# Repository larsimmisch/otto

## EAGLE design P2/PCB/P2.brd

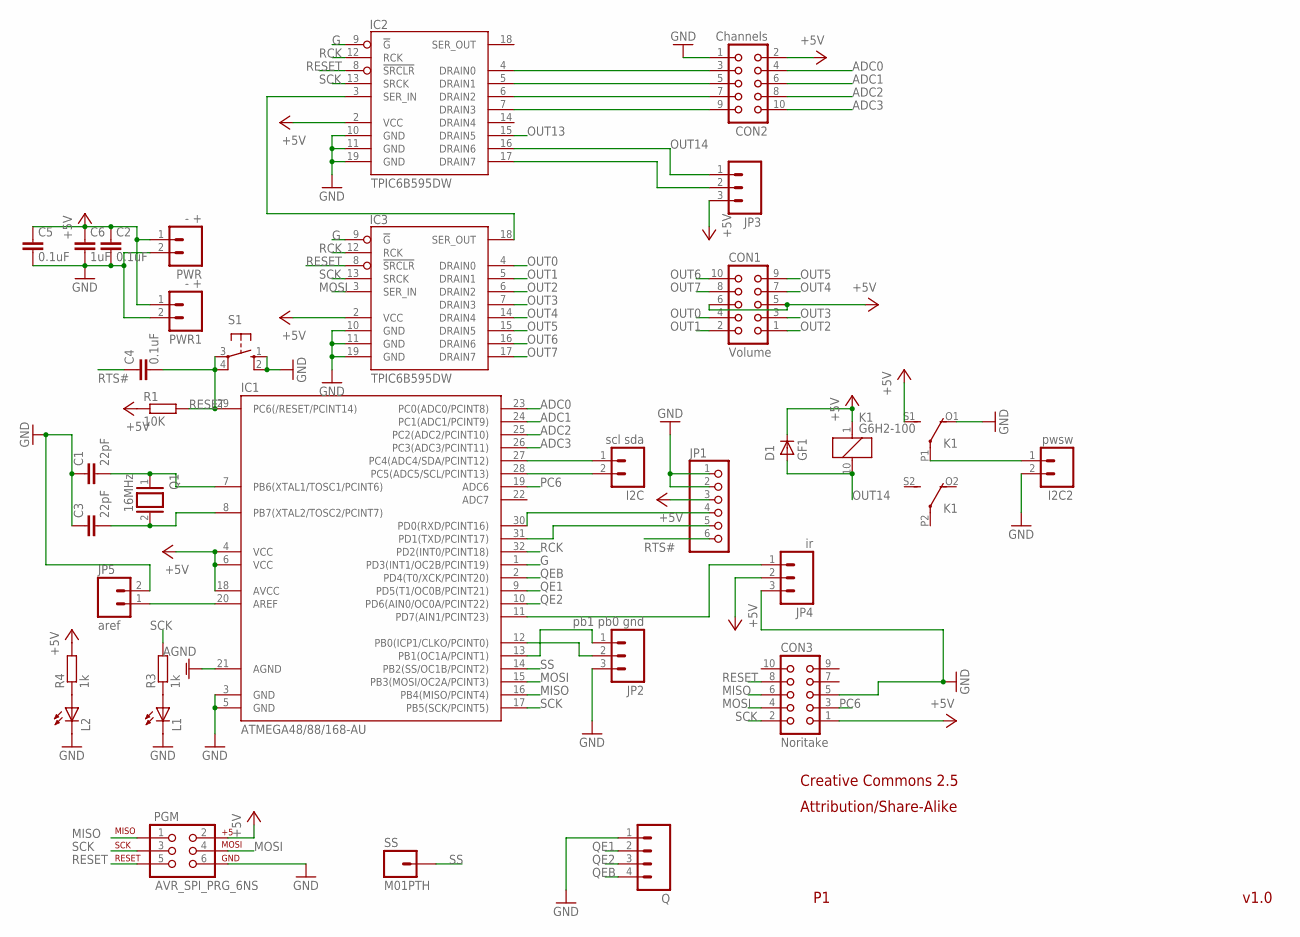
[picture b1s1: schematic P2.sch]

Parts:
C1, C3: 22pF; C0805
C2, C4, C5: 0.1uF; C0805
C6: 1uF; C0805
CON1: Volume; CON10L
CON2: Channels; CON10L
CON3: Noritake; CON10L
D1: GF1; SMA-DO214AC
I2C: scl sda; 1X02
I2C2: pwsw; 1X02
IC1: ATMEGA48/88/168-AU; TQFP32-08
IC2, IC3: TPIC6B595DW; SO20W
JP1: PINHD-1X6CLEAN; 1X06-CLEAN
JP2: pb1 pb0 gnd; 1X03
JP3: M03PTH; 1X03
JP4: ir; 1X03
JP5: aref; 1X02
K1: G6H2-100
L1, L2: LEDSML0805; SML0805
PGM: AVR_SPI_PRG_6NS; 2X3-NS
PWR, PWR1: - +; 1X02
Q: M04PTH; 1X04
Q1: 16MHz; QS
R1: 10K; M0805
R3, R4: 1k; M0805
S1: 10-XX; B3F-10XX
SS: M01PTH; 1X01

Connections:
+5V: C2.1, C5.1, C6.1, CON1.5, CON1.6, CON2.2, CON3.1, D1.K (C), IC1.4 (VCC), IC1.6 (VCC), IC1.18 (AVCC), IC2.2 (VCC), IC3.2 (VCC), JP1.3, JP3.3, JP4.2, K1.1, K1.S1 (S), PGM.2, PWR.1, PWR1.1, R1.1, R4.2
ADC0: CON2.4, IC1.23 (PC0(ADC0/PCINT8))
ADC1: CON2.6, IC1.24 (PC1(ADC1/PCINT9))
ADC2: CON2.8, IC1.25 (PC2(ADC2/PCINT10))
ADC3: CON2.10, IC1.26 (PC3(ADC3/PCINT11))
AGND: IC1.21 (AGND)
G: IC1.1 (PD3(INT1/OC2B/PCINT19)), IC2.9 (!G), IC3.9 (!G)
GND: C1.1, C2.2, C3.1, C5.2, C6.2, CON2.1, CON3.5, I2C2.2, IC1.3 (GND), IC1.5 (GND), IC2.10 (GND), IC2.11 (GND), IC2.19 (GND), IC3.10 (GND), IC3.11 (GND), IC3.19 (GND), JP1.1, JP1.2, JP2.3, JP4.3, JP5.2, K1.O1 (O), L1.C, L2.C, PGM.6, PWR.2, PWR1.2, Q.1, S1.1 (S), S1.2 (S1)
MISO: CON3.6, IC1.16 (PB4(MISO/PCINT4)), PGM.1
MOSI: CON3.4, IC1.15 (PB3(MOSI/OC2A/PCINT3)), IC3.3 (SER_IN), PGM.4
unnamed: C1.2, IC1.7 (PB6(XTAL1/TOSC1/PCINT6)), Q1.1
unnamed: C3.2, IC1.8 (PB7(XTAL2/TOSC2/PCINT7)), Q1.2
unnamed: IC1.30 (PD0(RXD/PCINT16)), JP1.4
unnamed: IC1.31 (PD1(TXD/PCINT17)), JP1.5
unnamed: I2C2.1, K1.P1
unnamed: IC2.3 (SER_IN), IC3.18 (SER_OUT)
unnamed: I2C.1, IC1.27 (PC4(ADC4/SDA/PCINT12))
unnamed: I2C.2, IC1.28 (PC5(ADC5/SCL/PCINT13))
unnamed: IC1.13 (PB1(OC1A/PCINT1)), JP2.1
unnamed: IC1.12 (PB0(ICP1/CLKO/PCINT0)), JP2.2
unnamed: IC2.17 (DRAIN7), JP3.2
unnamed: IC1.20 (AREF), JP5.1
unnamed: IC1.11 (PD7(AIN1/PCINT23)), JP4.1
unnamed: L1.A, R3.1
unnamed: L2.A, R4.1
OUT0: CON1.4, IC3.4 (DRAIN0)
OUT1: CON1.2, IC3.5 (DRAIN1)
OUT2: CON1.1, IC3.6 (DRAIN2)
OUT3: CON1.3, IC3.7 (DRAIN3)
OUT4: CON1.7, IC3.14 (DRAIN4)
OUT5: CON1.9, IC3.15 (DRAIN5)
OUT6: CON1.10, IC3.16 (DRAIN6)
OUT7: CON1.8, IC3.17 (DRAIN7)
OUT8: CON2.3, IC2.4 (DRAIN0)
OUT9: CON2.5, IC2.5 (DRAIN1)
OUT10: CON2.7, IC2.6 (DRAIN2)
OUT11: CON2.9, IC2.7 (DRAIN3)
OUT13: IC2.15 (DRAIN5)
OUT14: D1.A, IC2.16 (DRAIN6), JP3.1, K1.10 (2)
PC6: CON3.3, IC1.19 (ADC6)
QE1: IC1.9 (PD5(T1/OC0B/PCINT21)), Q.2
QE2: IC1.10 (PD6(AIN0/OC0A/PCINT22)), Q.3
QEB: IC1.2 (PD4(T0/XCK/PCINT20)), Q.4
RCK: IC1.32 (PD2(INT0/PCINT18)), IC2.12 (RCK), IC3.12 (RCK)
RESET: C4.2, CON3.8, IC1.29 (PC6(/RESET/PCINT14)), IC2.8 (!SRCLR), IC3.8 (!SRCLR), PGM.5, R1.2, S1.3, S1.4 (P1)
RTS#: C4.1, JP1.6
SCK: CON3.2, IC1.17 (PB5(SCK/PCINT5)), IC2.13 (SRCK), IC3.13 (SRCK), PGM.3, R3.2
SS: IC1.14 (PB2(SS/OC1B/PCINT2)), SS.1

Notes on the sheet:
v1.0
Creative Commons 2.5
Attribution/Share-Alike

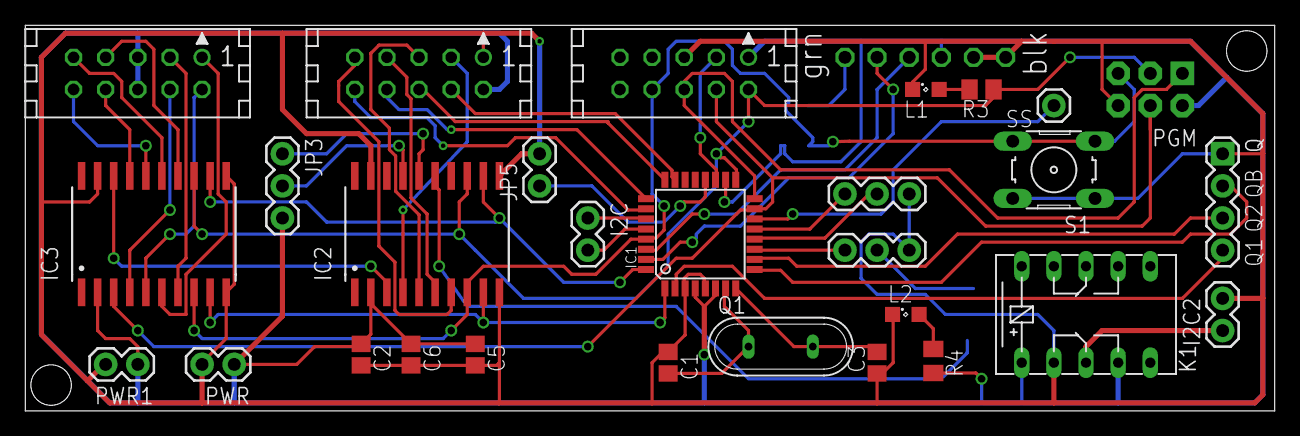
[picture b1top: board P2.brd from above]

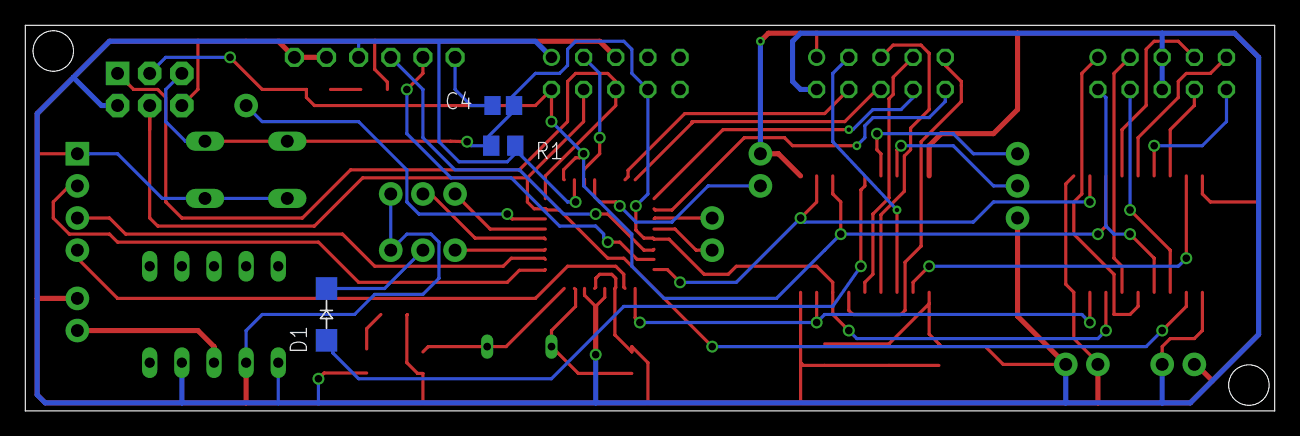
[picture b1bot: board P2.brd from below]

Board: 2 copper layers, 98.7 x 30.5 mm, 33 parts (3 on the bottom side), 46 nets.

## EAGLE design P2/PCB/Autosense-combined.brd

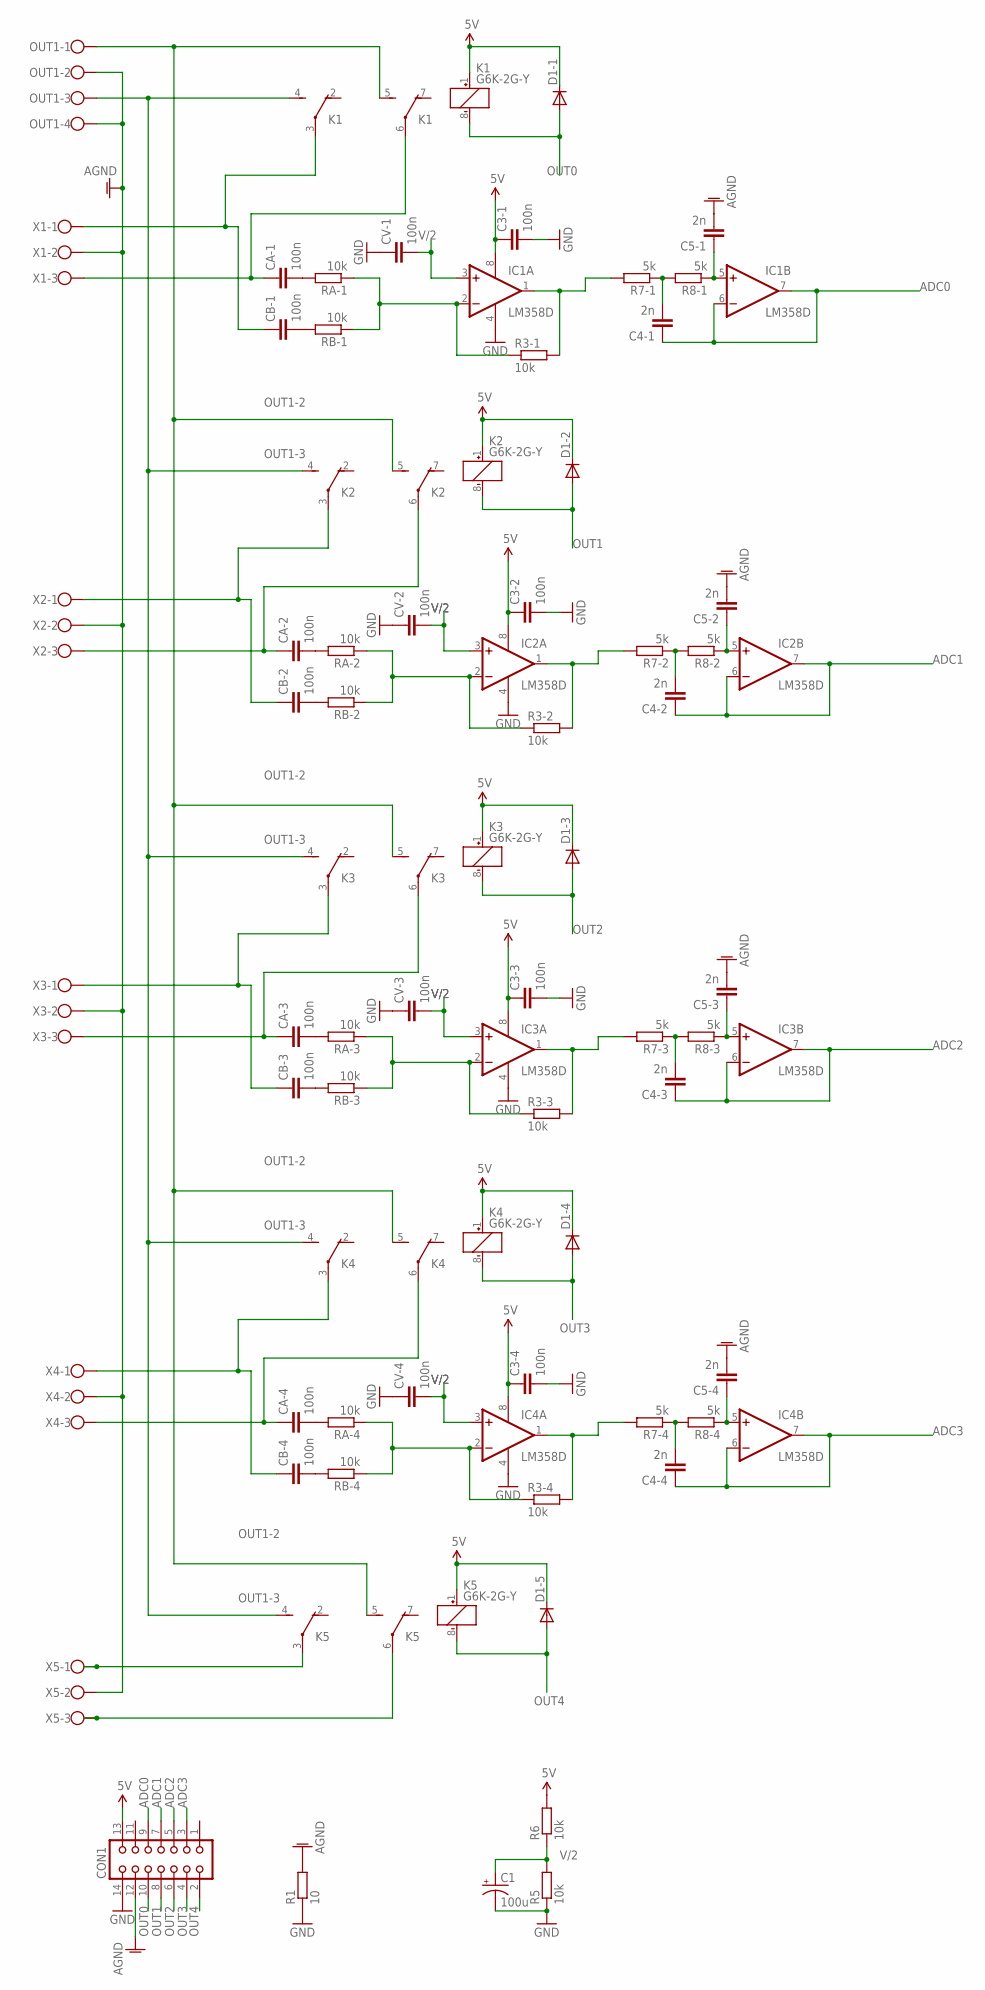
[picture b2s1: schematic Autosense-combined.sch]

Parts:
C1: 100u; CPOL-RADIAL-100UF-25V
C3-1, C3-2, C3-3, C3-4: 100n; C0805
C4-1, C4-2, C4-3, C4-4, C5-1, C5-2, C5-3, C5-4: 2n; C0805
CA-1, CA-2, CA-3, CA-4: 100n; C0805
CB-1, CB-2, CB-3, CB-4: 100n; C0805
CON1: CON14L
CV-1, CV-2, CV-3, CV-4: 100n; C0805
D1-1, D1-2, D1-3, D1-4, D1-5: DIODE-GF1; GF1
IC1, IC2, IC3, IC4: LM358D; SO08
K1, K2, K3, K4, K5: G6K-2G-Y
OUT1: W237-4
R1: 10; R1206
R3-1, R3-2, R3-3, R3-4, R5, R6: 10k; R0805
R7-1, R7-2, R7-3, R7-4, R8-1, R8-2, R8-3, R8-4: 5k; R0805
RA-1, RA-2, RA-3, RA-4: 10k; R0805
RB-1, RB-2, RB-3, RB-4: 10k; M0805
X1, X2, X3, X4, X5: W237-103

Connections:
5V: C3-1.1, C3-2.1, C3-3.1, C3-4.1, CON1.13, D1-1.C, D1-2.C, D1-3.C, D1-4.C, D1-5.C, IC1.8 (V+), IC2.8 (V+), IC3.8 (V+), IC4.8 (V+), K1.1 (+), K2.1 (+), K3.1 (+), K4.1 (+), K5.1 (+), R6.2
$NET1: CB-2.1, K2.3, X2.1
$NET2: CB-3.1, K3.3, X3.1
$NET3: CB-4.1, K4.3, X4.1
$NET4: K5.3, X5.1
$NET13: CB-1.1, K1.3, X1.1
ADC0: C4-1.1, CON1.9, IC1.6 (-IN), IC1.7 (OUT)
ADC1: C4-2.1, CON1.7, IC2.6 (-IN), IC2.7 (OUT)
ADC2: C4-3.1, CON1.5, IC3.6 (-IN), IC3.7 (OUT)
ADC3: C4-4.1, CON1.3, IC4.6 (-IN), IC4.7 (OUT)
AGND: C5-1.2, C5-2.2, C5-3.2, C5-4.2, CON1.12, OUT1.2, OUT1.4, R1.2, X1.2, X2.2, X3.2, X4.2, X5.2
GND: C1.2 (-), C3-1.2, C3-2.2, C3-3.2, C3-4.2, CON1.14, CV-1.1, CV-2.1, CV-3.1, CV-4.1, IC1.4 (V-), IC2.4 (V-), IC3.4 (V-), IC4.4 (V-), R1.1, R5.1
unnamed: CA-1.1, K1.6, X1.3
unnamed: C5-1.1, IC1.5 (+IN), R8-1.1
unnamed: IC3.1 (OUT), R3-3.2, R7-3.2
unnamed: IC3.2 (-IN), R3-3.1, RA-3.1, RB-3.1
unnamed: C5-3.1, IC3.5 (+IN), R8-3.1
unnamed: IC1.2 (-IN), R3-1.1, RA-1.1, RB-1.1
unnamed: IC2.1 (OUT), R3-2.2, R7-2.2
unnamed: C4-1.2, R7-1.1, R8-1.2
unnamed: IC1.1 (OUT), R3-1.2, R7-1.2
unnamed: IC2.2 (-IN), R3-2.1, RA-2.1, RB-2.1
unnamed: CA-1.2, RA-1.2
unnamed: C5-2.1, IC2.5 (+IN), R8-2.1
unnamed: CB-1.2, RB-1.2
unnamed: C4-2.2, R7-2.1, R8-2.2
unnamed: C4-3.2, R7-3.1, R8-3.2
unnamed: CA-3.2, RA-3.2
unnamed: CA-2.2, RA-2.2
unnamed: CB-2.2, RB-2.2
unnamed: CA-2.1, K2.6, X2.3
unnamed: CB-3.2, RB-3.2
unnamed: CA-3.1, K3.6, X3.3
unnamed: IC4.1 (OUT), R3-4.2, R7-4.2
unnamed: IC4.2 (-IN), R3-4.1, RA-4.1, RB-4.1
unnamed: C5-4.1, IC4.5 (+IN), R8-4.1
unnamed: C4-4.2, R7-4.1, R8-4.2
unnamed: CA-4.2, RA-4.2
unnamed: CB-4.2, RB-4.2
unnamed: CA-4.1, K4.6, X4.3
unnamed: K5.6, X5.3
OUT0: CON1.10, D1-1.A, K1.8 (-)
OUT1: CON1.8, D1-2.A, K2.8 (-)
OUT1-2: K1.5 (S), K2.5 (S), K3.5 (S), K4.5 (S), K5.5 (S), OUT1.1
OUT1-3: K1.4 (S), K2.4 (S), K3.4 (S), K4.4 (S), K5.4 (S), OUT1.3
OUT2: CON1.6, D1-3.A, K3.8 (-)
OUT3: CON1.4, D1-4.A, K4.8 (-)
OUT4: CON1.2, D1-5.A, K5.8 (-)
V/2: C1.1 (+), CV-1.2, CV-2.2, CV-3.2, CV-4.2, IC1.3 (+IN), IC2.3 (+IN), IC3.3 (+IN), IC4.3 (+IN), R5.2, R6.1

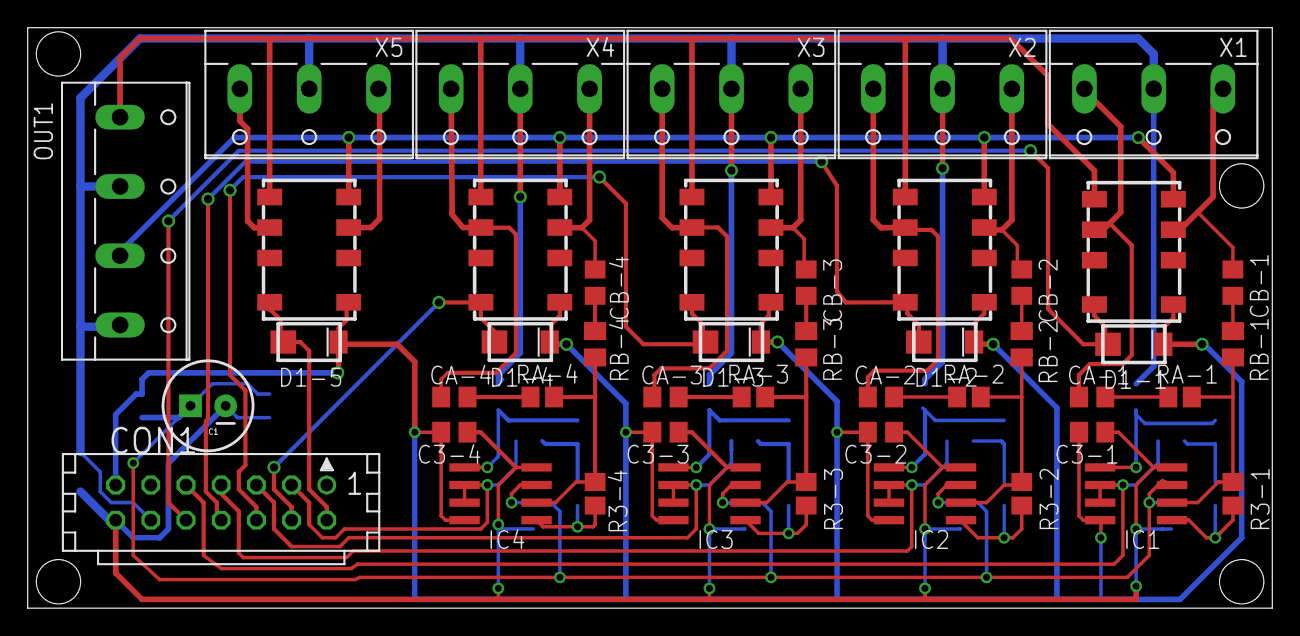
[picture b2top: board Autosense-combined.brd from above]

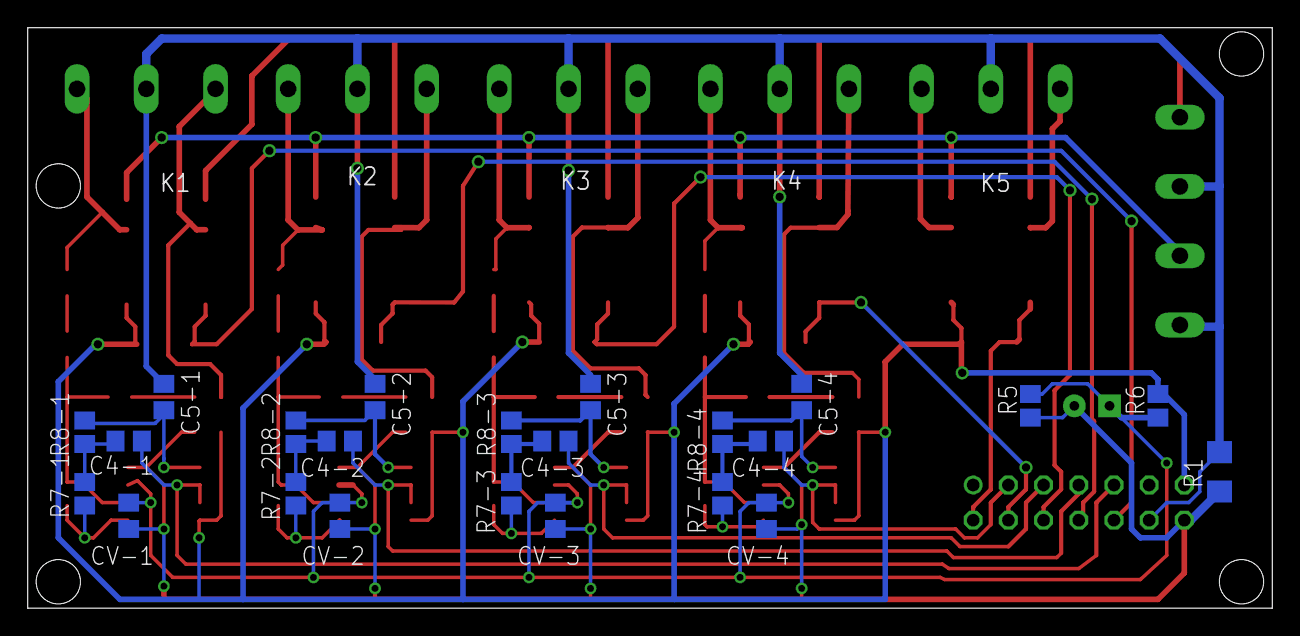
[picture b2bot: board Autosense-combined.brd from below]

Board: 2 copper layers, 89.8 x 41.9 mm, 69 parts (23 on the bottom side), 49 nets.

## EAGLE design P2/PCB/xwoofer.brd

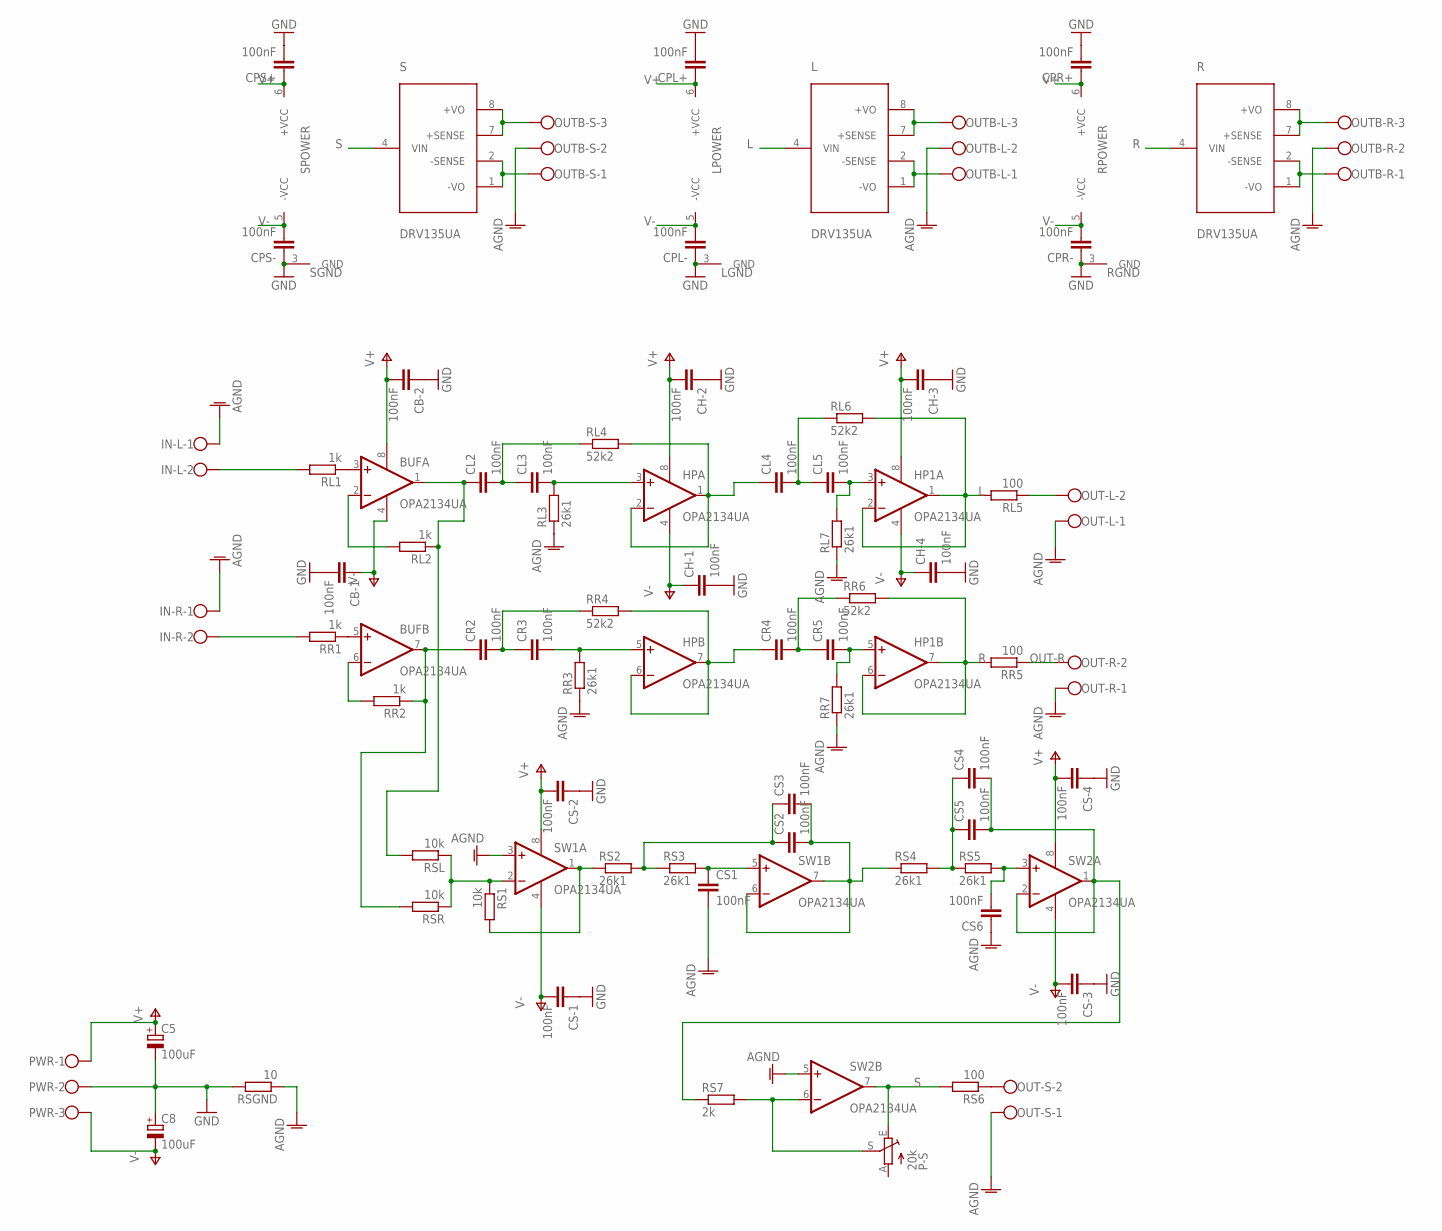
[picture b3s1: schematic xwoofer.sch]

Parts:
BUF: OPA2134UA; SO08
C5, C8: 100uF; E2,5-7
CB-1, CB-2: 100nF; C0805
CH-1, CH-2, CH-3, CH-4: 100nF; C0805K
CL2, CL3, CL4, CL5: 100nF; C025-025X050
CPL+: 100nF; C0805K
CPL-: 100nF; C0805K
CPR+: 100nF; C0805K
CPR-: 100nF; C0805K
CPS+: 100nF; C0805K
CPS-: 100nF; C0805K
CR2, CR3, CR4, CR5: 100nF; C025-025X050
CS1, CS2, CS3, CS4, CS5, CS6: 100nF; C025-025X050
CS-1, CS-2, CS-3, CS-4: 100nF; C0805K
HP, HP1: OPA2134UA; SO08
IN-L: W237-102
IN-R: W237-102
L: DRV135UA; SO08
OUT-L: W237-102
OUT-R: W237-102
OUT-S: W237-102
OUTB-L: W237-103
OUTB-R: W237-103
OUTB-S: W237-103
P-S: 20k; B64Y
PWR: W237-103
R: DRV135UA; SO08
RL1, RL2: 1k; R0603
RL3, RL7: 26k1; R0603
RL4, RL6: 52k2; R0603
RL5: 100; R1206
RR1, RR2: 1k; R0603
RR3, RR7: 26k1; R0603
RR4, RR6: 52k2; R0603
RR5: 100; R1206
RS1: 10k; R0603
RS2, RS3, RS4, RS5: 26k1; R0603
RS6: 100; R1206
RS7: 2k; R0603
RSGND: 10; R1206
RSL: 10k; R0603
RSR: 10k; R0603
S: DRV135UA; SO08
SW1, SW2: OPA2134UA; SO08

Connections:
AGND: CS1.2, CS6.1, IN-L.1, IN-R.1, OUT-L.1, OUT-R.1, OUT-S.1, OUTB-L.2, OUTB-R.2, OUTB-S.2, RL3.1, RL7.1, RR3.1, RR7.1, RSGND.1, SW1.3 (+IN), SW2.5 (+IN)
CL3: CL3.2, HP.3 (+IN), RL3.2
GND: C5.-, C8.+, CB-1.2, CB-2.1, CH-1.2, CH-2.1, CH-3.1, CH-4.2, CPL+.2, CPL-.1, CPR+.2, CPR-.1, CPS+.2, CPS-.1, CS-1.1, CS-2.1, CS-3.1, CS-4.1, L.3 (GND), PWR.2, R.3 (GND), RSGND.2, S.3 (GND)
L: HP1.1 (OUT), HP1.2 (-IN), L.4 (VIN), RL5.2, RL6.2
unnamed: OUT-S.2, RS6.1
unnamed: RS1.1, RSL.1, RSR.1, SW1.2 (-IN)
unnamed: RS1.2, RS2.1, SW1.1 (OUT)
unnamed: IN-L.2, RL1.2
unnamed: IN-R.2, RR1.2
unnamed: BUF.2 (-IN), RL2.2
unnamed: CL4.2, CL5.1, RL6.1
unnamed: CL2.2, CL3.1, RL4.1
unnamed: BUF.7 (OUT), CR2.1, RR2.1, RSR.2
unnamed: OUT-L.2, RL5.1
unnamed: BUF.3 (+IN), RL1.1
unnamed: BUF.5 (+IN), RR1.1
unnamed: CS2.1, CS3.1, RS2.2, RS3.1
unnamed: CL5.2, HP1.3 (+IN), RL7.2
unnamed: L.7 (+SENSE), L.8 (+VO), OUTB-L.3
unnamed: CS1.1, RS3.2, SW1.5 (+IN)
unnamed: BUF.6 (-IN), RR2.2
unnamed: CR4.2, CR5.1, RR6.1
unnamed: CS4.1, CS5.1, RS4.2, RS5.1
unnamed: CR5.2, HP1.5 (+IN), RR7.2
unnamed: L.1 (-VO), L.2 (-SENSE), OUTB-L.1
unnamed: OUTB-R.3, R.7 (+SENSE), R.8 (+VO)
unnamed: CS4.2, CS5.2, RS7.1, SW2.1 (OUT), SW2.2 (-IN)
unnamed: CS6.2, RS5.2, SW2.3 (+IN)
unnamed: CR3.2, HP.5 (+IN), RR3.2
unnamed: P-S.S, RS7.2, SW2.6 (-IN)
unnamed: CL4.1, HP.1 (OUT), HP.2 (-IN), RL4.2
unnamed: CR4.1, HP.6 (-IN), HP.7 (OUT), RR4.2
unnamed: CR2.2, CR3.1, RR4.1
unnamed: BUF.1 (OUT), CL2.1, RL2.1, RSL.2
unnamed: OUTB-R.1, R.1 (-VO), R.2 (-SENSE)
unnamed: OUTB-S.3, S.7 (+SENSE), S.8 (+VO)
unnamed: OUTB-S.1, S.1 (-VO), S.2 (-SENSE)
OUT-R: OUT-R.2, RR5.1
R: HP1.6 (-IN), HP1.7 (OUT), R.4 (VIN), RR5.2, RR6.2
S: P-S.E, RS6.2, S.4 (VIN), SW2.7 (OUT)
SF: CS2.2, CS3.2, RS4.1, SW1.6 (-IN), SW1.7 (OUT)
V+: BUF.8 (V+), C5.+, CB-2.2, CH-2.2, CH-3.2, CPL+.1, CPR+.1, CPS+.1, CS-2.2, CS-4.2, HP.8 (V+), HP1.8 (V+), L.6 (+VCC), PWR.1, R.6 (+VCC), S.6 (+VCC), SW1.8 (V+), SW2.8 (V+)
V-: BUF.4 (V-), C8.-, CB-1.1, CH-1.1, CH-4.1, CPL-.2, CPR-.2, CPS-.2, CS-1.2, CS-3.2, HP.4 (V-), HP1.4 (V-), L.5 (-VCC), PWR.3, R.5 (-VCC), S.5 (-VCC), SW1.4 (V-), SW2.4 (V-)

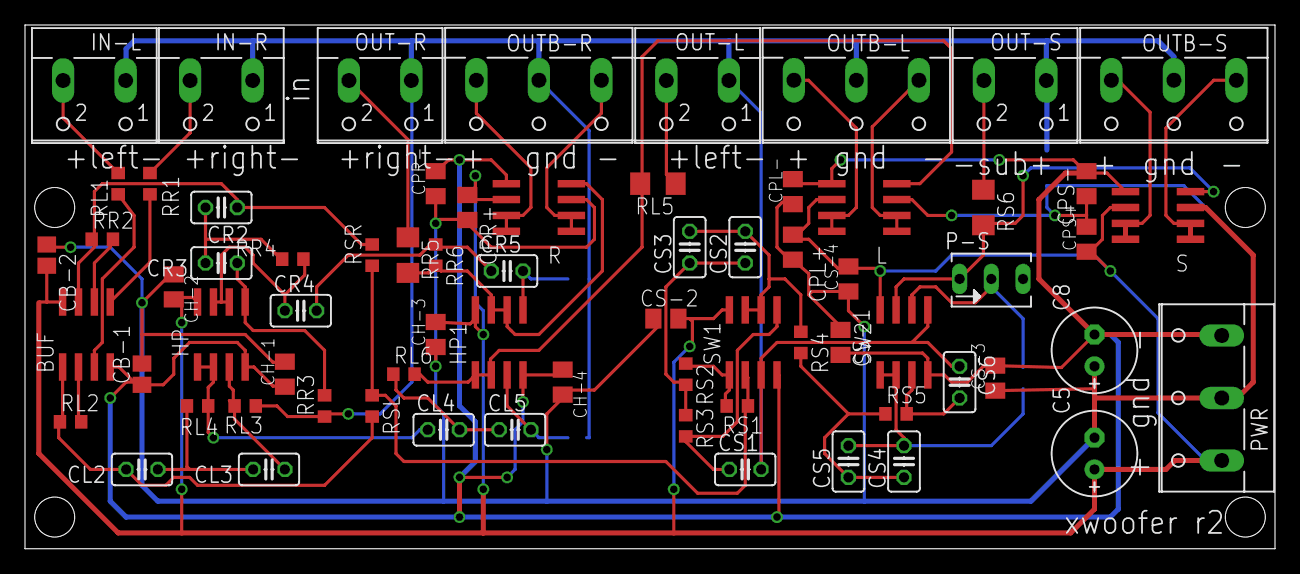
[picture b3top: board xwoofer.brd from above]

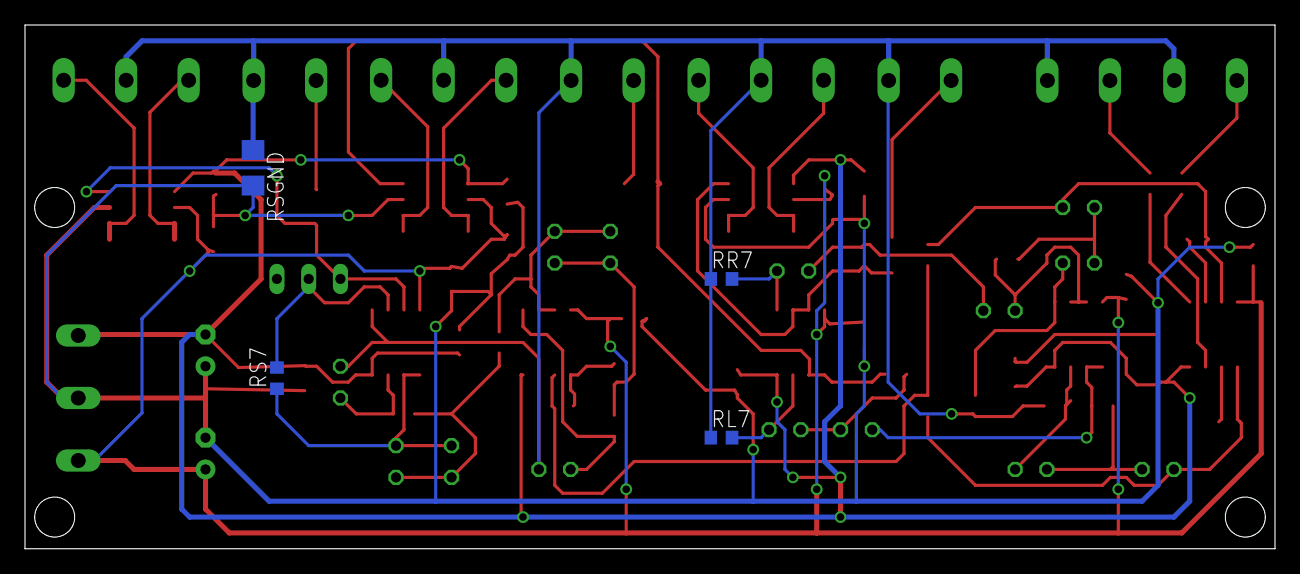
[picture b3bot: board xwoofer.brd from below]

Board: 2 copper layers, 100.0 x 41.9 mm, 74 parts (4 on the bottom side), 43 nets.

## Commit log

2011-12-19 Added blink example with arduino-- as a submodule.
    Untested, but hey, it even links.
2013-04-16 Added P2; Basic display and Quad encoder working.
    Volume display is incomplete.
2013-05-19 Initial working version.
    - No Autosense
    - No IR command decoding from Squeezebox
2013-05-30 P2 routed
2013-05-30 Remove unused reverse
2013-05-31 Added AutoSense, missing connections on P2
2013-06-03 Jumper for IR and SS, silkscreen cleanups.
2013-06-06 ADC seems to be working
2013-06-06 Connect AVCC
2013-06-06 Added AREF Jumper
2013-06-07 Add silkscreen for UART
2013-06-28 xwoofer crossover with 24db/octave and star ground
    xwoofer routed, design rules passed, not pretty
2013-08-12 Added USB breakout board
2014-02-07 Briefly explain CombiController
2014-05-10 Autosense 4+1 channels complete
2014-05-10 Add project name
2014-05-10 small silkscreen fixes
2016-01-12 Add test_spi
2016-01-12 Added ipod-female-breakout
2017-04-24 Added heat chamber (wip)
2017-04-25 Support degree symbol
2017-04-25 Simplify: the Squeezebox fonts are latin-1
    But don't generate latin-1 literals, C sourcecode needs to use hex constants for latin-1 characters beyond ASCII 7 bit.
2017-05-05 Support larger fonts
2017-05-05 Quadrature encoder working.
2017-05-05 Half degree steps
2017-05-06 Use floats - we'll need them for the PID anyway.
2018-02-12 P2 PCB update for peakdetect.
2018-04-02 Add anchor for submodule
2018-04-02 New FTDI - remove dead PCB for AutoSense
2018-04-03 Remove MAkefile.local
2018-04-04 Connect pin 3 of the serial connector to power. Doh.
2018-04-04 Flip channel connector
2018-04-15 Working version with heavily patched PCB
    - ADC6 does not work as /SS for Noritake, use B0.
    - Relay connected wrong (internal diode!)
2019-05-26 Addcapacitive humidity sensor
2023-05-02 Makefie fix
2023-05-02 Fix out-of-bounds access and area
2023-05-02 Fix port assignments, dimmer is working (but flickering badly)
2023-06-05 Replace phase control with a relay
2023-06-06 Working ok with the relay
2023-06-06 Hysteresis was too hysterical
2023-06-06 Proper hysteresis. 0.1 is still a bit fast, too
2023-06-09 Show indicator when writing to EEPROM

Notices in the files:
parts and their libraries:
SparkFun-Connectors: Licensing: CC v3.0 Share-Alike You are welcome to use this library for commercial purposes.
